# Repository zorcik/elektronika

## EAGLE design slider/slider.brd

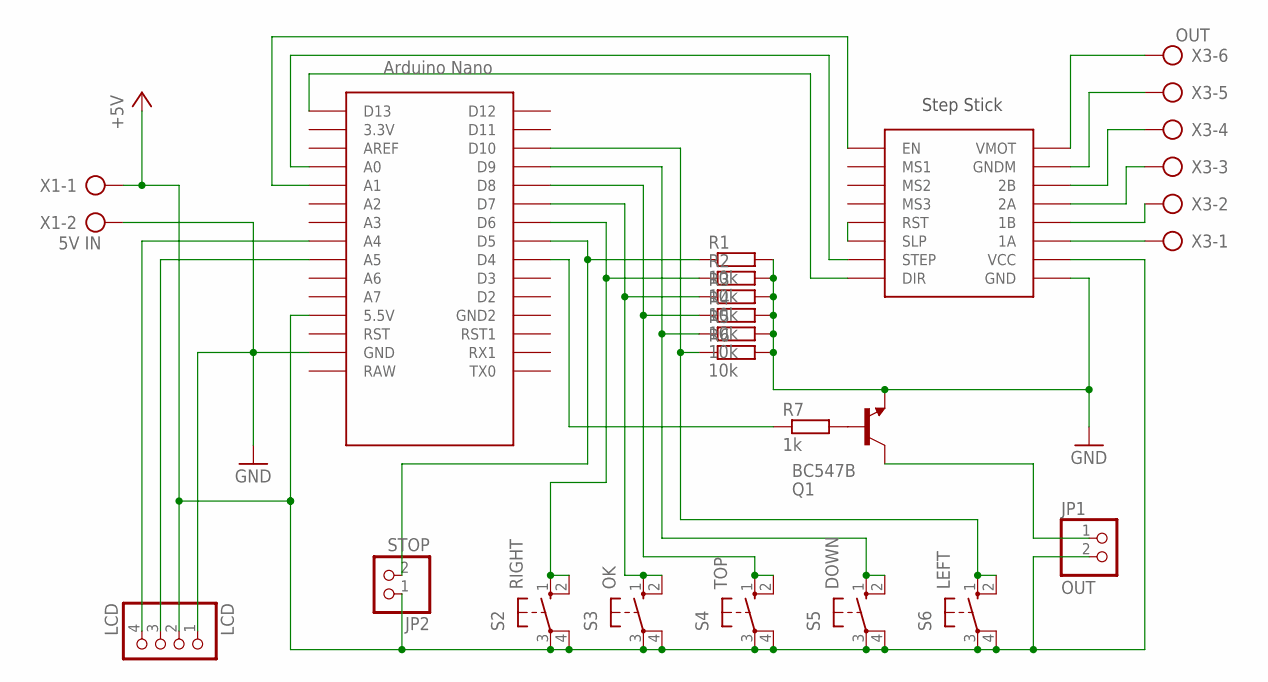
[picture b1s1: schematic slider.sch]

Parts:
JP1: OUT; 1X02
JP2: STOP; 1X02
LCD: LCD; 1X04
Q1: BC547B; TO92
R1, R2, R3, R4, R5, R6: 10k; 0207/10
R7: 1k; 0207/10
S2: RIGHT; B3F-10XX
S3: OK; B3F-10XX
S4: TOP; B3F-10XX
S5: DOWN; B3F-10XX
S6: LEFT; B3F-10XX
U$1: NANO
U$2: STEP-STICK
X1: 5V IN; AK500/2
X3: OUT; AK500/6

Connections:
+5V: JP1.2, JP2.1, LCD.2, S2.3, S2.4 (P1), S3.3, S3.4 (P1), S4.3, S4.4 (P1), S5.3, S5.4 (P1), S6.3, S6.4 (P1), U$1.5V (5.5V), U$2.VCC, X1.1
GND: LCD.1, Q1.1 (E), R1.2, R2.2, R3.2, R4.2, R5.2, R6.2, U$1.GND, U$2.GND, X1.2
unnamed: U$2.1A, X3.1
unnamed: U$2.1B, X3.2
unnamed: U$2.2A, X3.3
unnamed: U$2.2B, X3.4
unnamed: U$2.GNDM, X3.5
unnamed: U$2.VMOT, X3.6
unnamed: U$1.A0, U$2.SPT (STEP)
unnamed: LCD.4, U$1.A4
unnamed: LCD.3, U$1.A5
unnamed: U$1.D13, U$2.DIR
unnamed: JP2.2, R1.1, U$1.D5
unnamed: R2.1, S2.1 (S), S2.2 (S1), U$1.D6
unnamed: R3.1, S3.1 (S), S3.2 (S1), U$1.D7
unnamed: R4.1, S4.1 (S), S4.2 (S1), U$1.D8
unnamed: R5.1, S5.1 (S), S5.2 (S1), U$1.D9
unnamed: R6.1, S6.1 (S), S6.2 (S1), U$1.D10
unnamed: U$2.RST, U$2.SLP
unnamed: R7.1, U$1.D4
unnamed: Q1.2 (B), R7.2
unnamed: U$1.A1, U$2.EN
unnamed: JP1.1, Q1.3 (C)

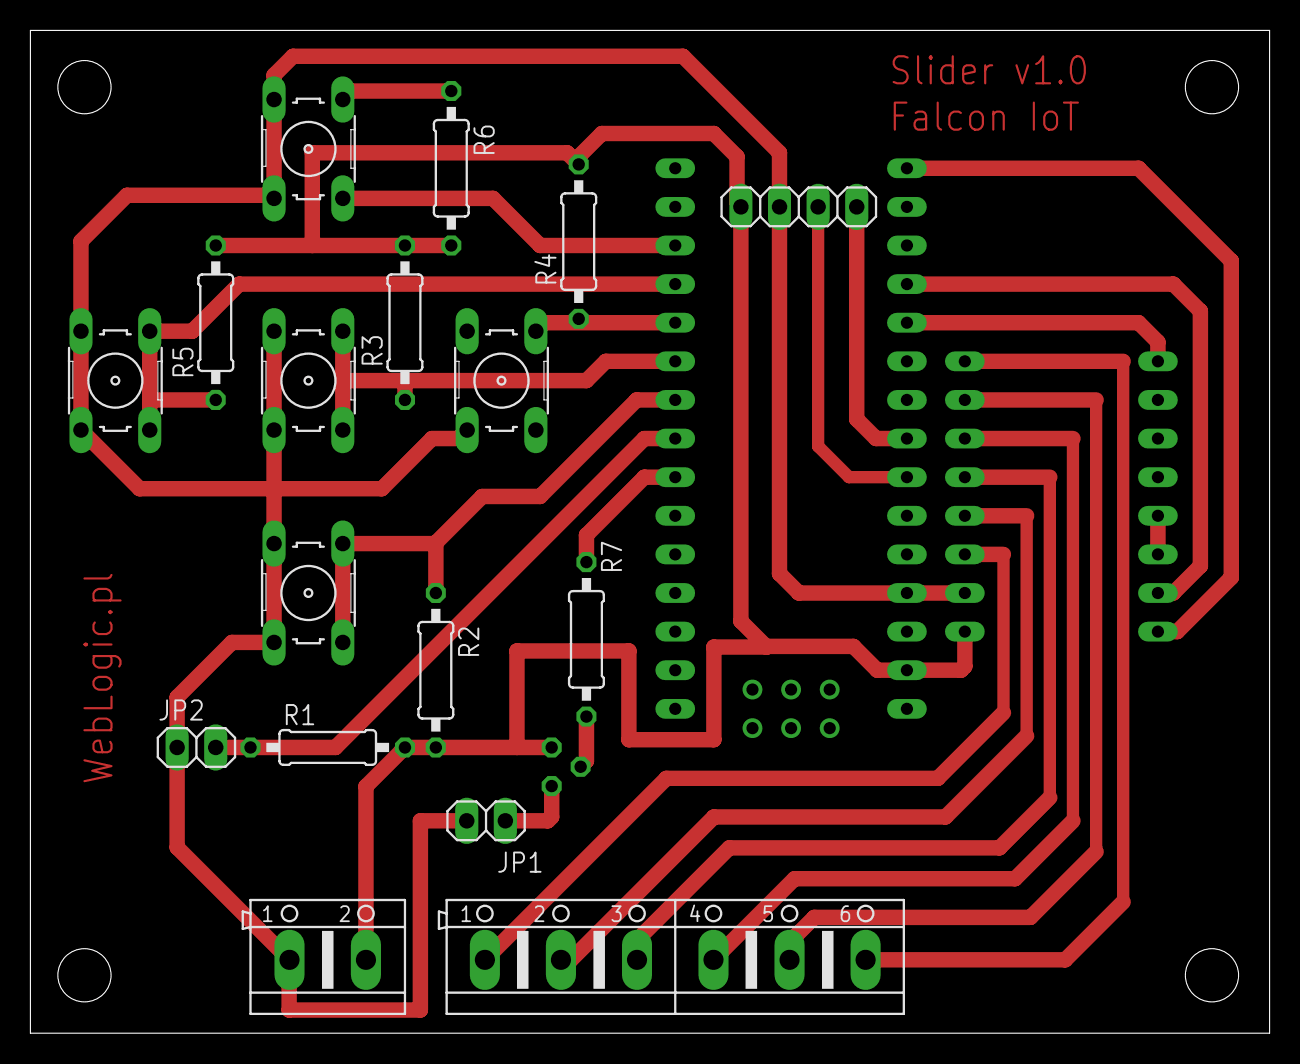
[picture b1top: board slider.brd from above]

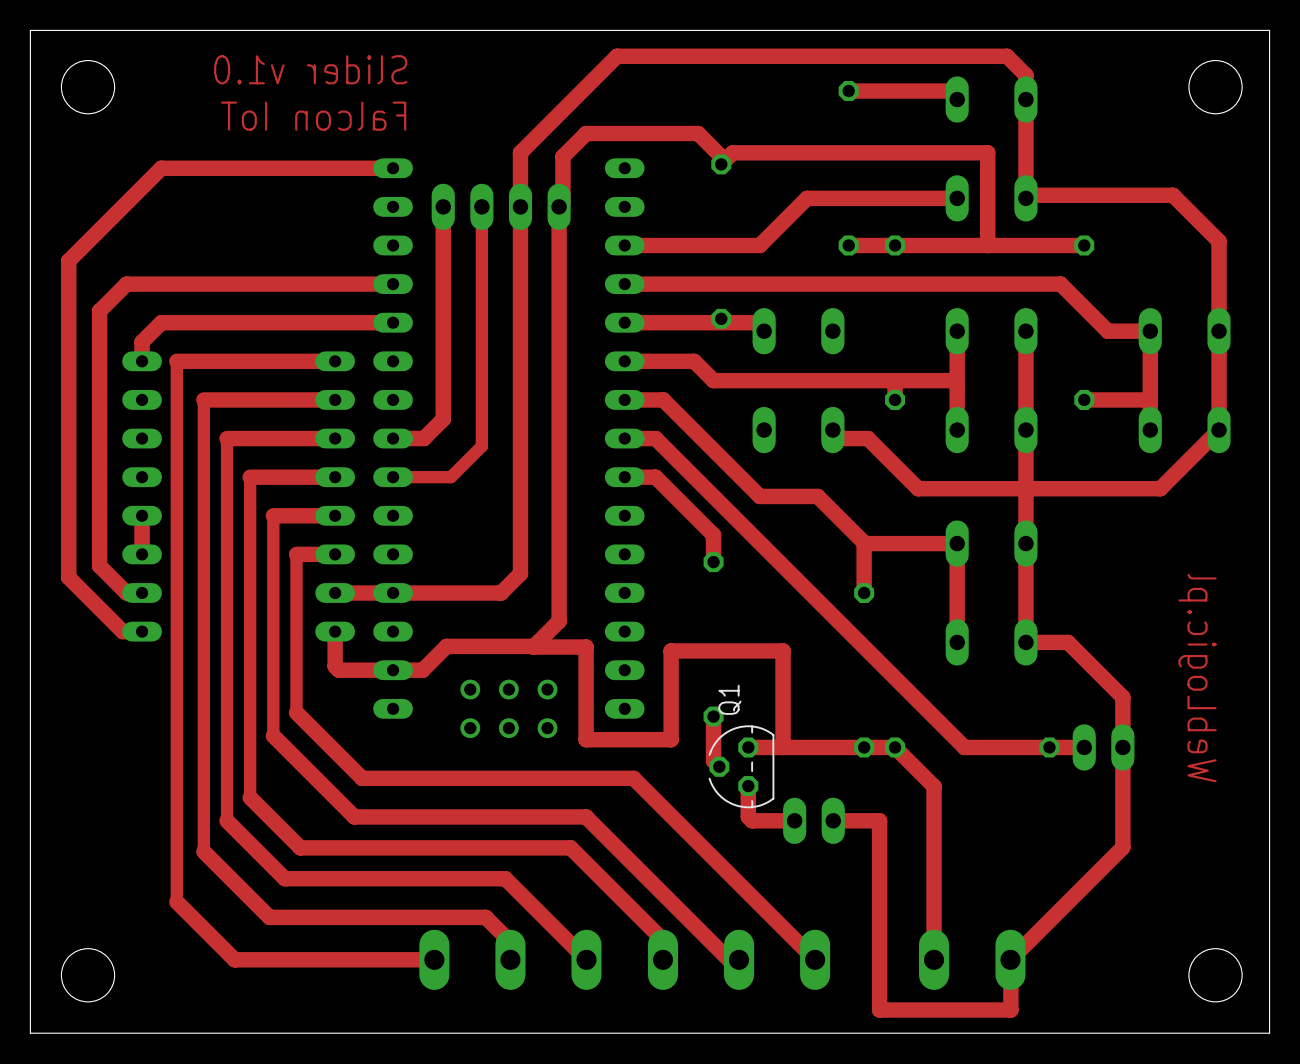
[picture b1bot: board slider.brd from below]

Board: 2 copper layers, 81.5 x 66.0 mm, 20 parts (2 on the bottom side), 23 nets.

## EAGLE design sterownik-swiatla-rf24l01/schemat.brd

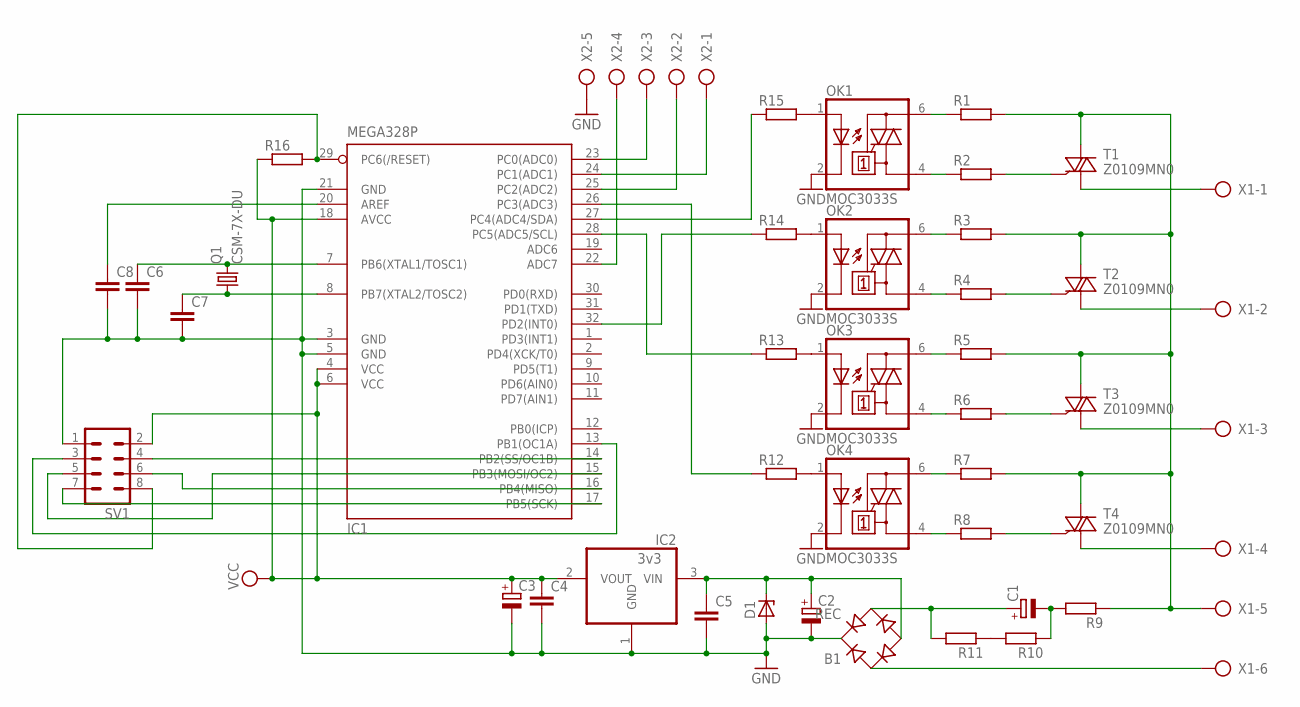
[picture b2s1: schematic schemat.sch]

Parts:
B1: REC; B40S
C1: CPOL-EU139CLL-2W; 139CLL-2W
C2, C3: CPOL-EU140CLH-1010; 140CLH-1010
C4, C5, C6, C7, C8: C-EUC1210; C1210
D1: ZENER-DIODESMB; SMB
IC1: MEGA328P; TQFP32-08
IC2: 3v3; SOT223
OK1, OK2, OK3, OK4: MOC3033S; DIL6-SMD
Q1: CSM-7X-DU
R1, R2, R3, R4, R5, R6, R7, R8, R12, R13, R14, R15, R16: RR1206; R1206
R9: RR2512; R2512
R10, R11: RR1210; R1210
SV1: MA04-2
T1, T2, T3, T4: Z0109MN0; SOT223
X1: AK500/6
X2: AK300/5

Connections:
GND: B1.+, C2.-, C3.-, C4.2, C5.2, C6.2, C7.2, C8.2, D1.A, IC1.3 (GND), IC1.5 (GND), IC1.21 (GND), IC2.1 (GND), OK1.2 (C), OK2.2 (C), OK3.2 (C), OK4.2 (C), SV1.1, X2.5
unnamed: IC1.24 (PC1(ADC1)), X2.1
unnamed: R2.2, T1.3 (G)
unnamed: OK1.6 (A2), R1.1
unnamed: OK1.4 (A1), R2.1
unnamed: OK2.6 (A2), R3.1
unnamed: OK2.4 (A1), R4.1
unnamed: OK3.6 (A2), R5.1
unnamed: OK3.4 (A1), R6.1
unnamed: OK4.6 (A2), R7.1
unnamed: OK4.4 (A1), R8.1
unnamed: R8.2, T4.3 (G)
unnamed: IC1.23 (PC0(ADC0)), X2.3
unnamed: R6.2, T3.3 (G)
unnamed: R4.2, T2.3 (G)
unnamed: R1.2, R3.2, R5.2, R7.2, R9.1, T1.1 (LD), T2.1 (LD), T3.1 (LD), T4.1 (LD), X1.5
unnamed: IC1.32 (PD2(INT0)), R14.1
unnamed: R10.2, R11.1
unnamed: C1.-, R9.2, R10.1
unnamed: B1.AC2, C1.+, R11.2
unnamed: B1.AC1, X1.6
unnamed: B1.-, C2.+, C5.1, D1.C, IC2.3 (VIN)
unnamed: T4.2 (CM), T4.4 (CM), X1.4
unnamed: T3.2 (CM), T3.4 (CM), X1.3
unnamed: OK4.1 (A), R12.2
unnamed: OK3.1 (A), R13.2
unnamed: OK2.1 (A), R14.2
unnamed: OK1.1 (A), R15.2
unnamed: C6.1, IC1.7 (PB6(XTAL1/TOSC1)), Q1.2
unnamed: C7.1, IC1.8 (PB7(XTAL2/TOSC2)), Q1.1
unnamed: T2.2 (CM), T2.4 (CM), X1.2
unnamed: IC1.26 (PC3(ADC3)), R12.1
unnamed: IC1.28 (PC5(ADC5/SCL)), R13.1
unnamed: IC1.13 (PB1(OC1A)), SV1.3
unnamed: IC1.27 (PC4(ADC4/SDA)), R15.1
unnamed: IC1.25 (PC2(ADC2)), X2.2
unnamed: IC1.22 (ADC7), X2.4
unnamed: C8.1, IC1.20 (AREF)
unnamed: T1.2 (CM), T1.4 (CM), X1.1
unnamed: IC1.14 (PB2(SS/OC1B)), SV1.4
unnamed: IC1.15 (PB3(MOSI/OC2)), SV1.5
unnamed: IC1.16 (PB4(MISO)), SV1.6
unnamed: IC1.17 (PB5(SCK)), SV1.7
unnamed: IC1.29 (PC6(/RESET)), R16.2, SV1.8
VCC: C3.+, C4.1, IC1.4 (VCC), IC1.6 (VCC), IC1.18 (AVCC), IC2.2 (VOUT), R16.1, SV1.2

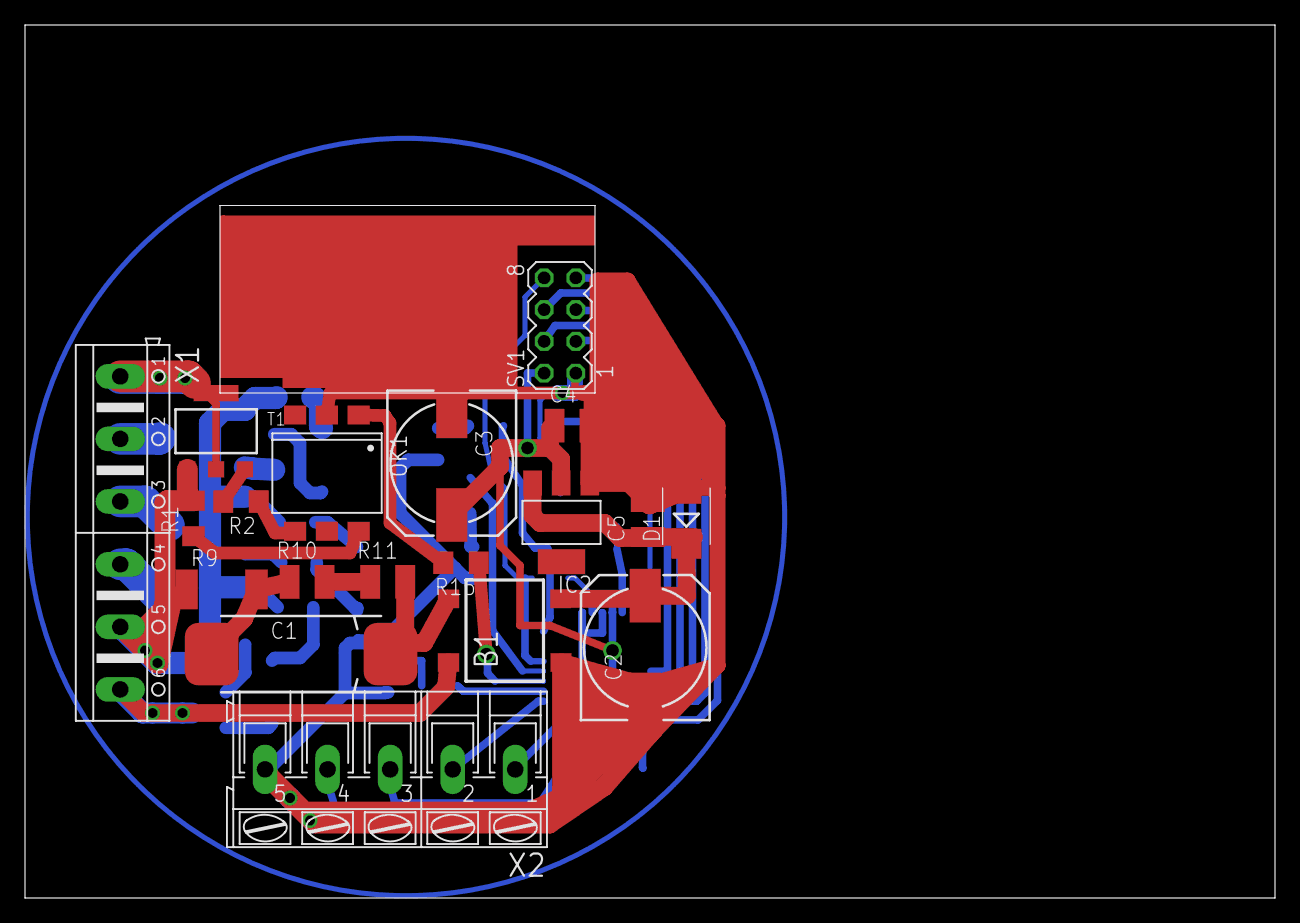
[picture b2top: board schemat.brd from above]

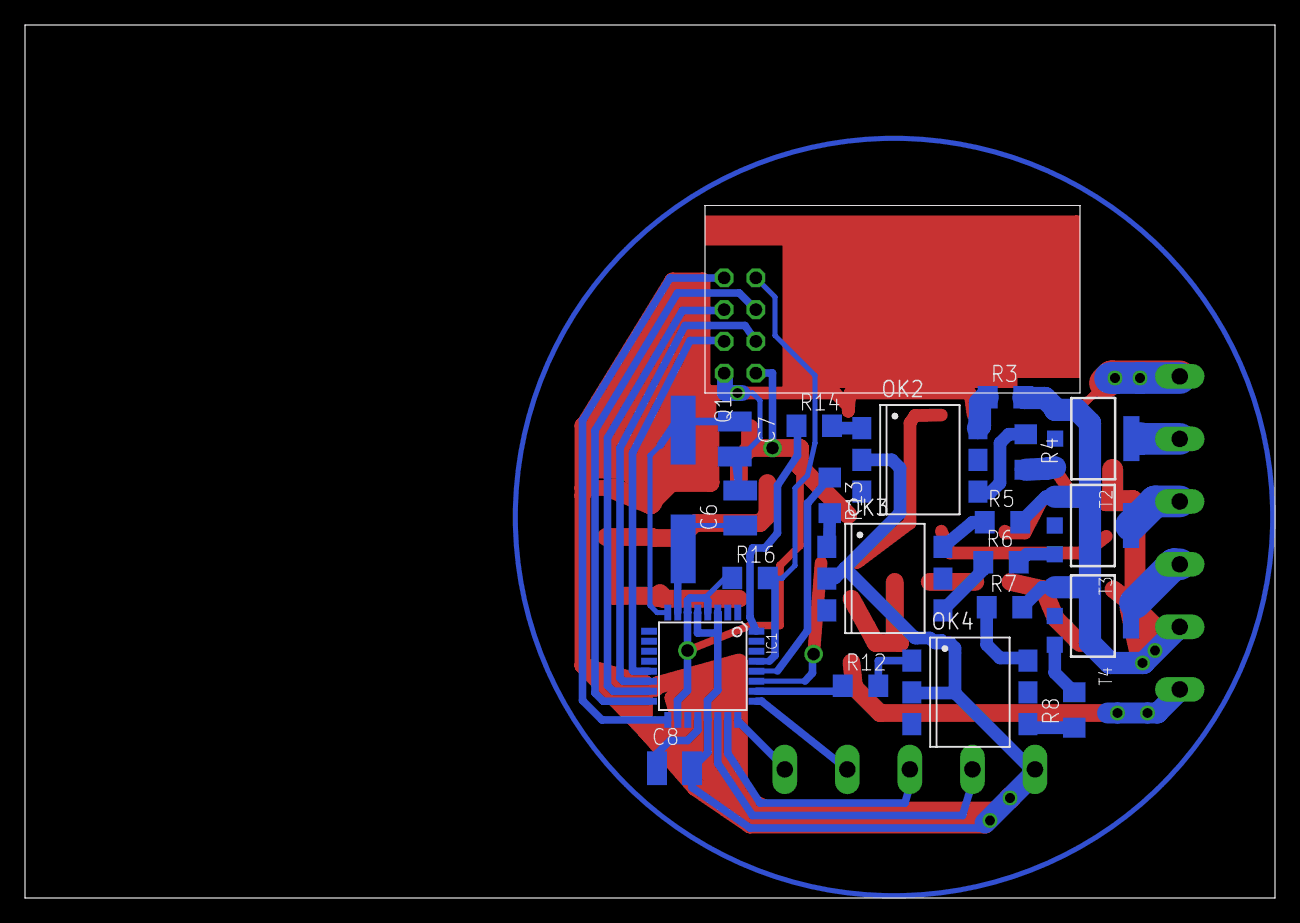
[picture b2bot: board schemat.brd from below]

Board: 2 copper layers, 100.0 x 69.8 mm, 40 parts (21 on the bottom side), 45 nets.
